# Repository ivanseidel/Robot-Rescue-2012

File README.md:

Robot-Rescue-2012
=================

This repository includes the entire Rescue B project from 2012, used in the international RoboCup Rescue B league.
Our team could acomplish the 3th place in super-team and 1st place of robot design.

There is a currently new version of it (on the picture, the 2013 one), find out more [here](https://github.com/ivanseidel/Robot-Rescue-2013).

This robot was the first Android based robot, that used the cellphone as the main processor and could controll the entirely the robot. We could acomplish heavy calculations using Android's 2.4Ghz processor, creating really "expensive" euristics.

The software has about 12.000 lines of code, written in Java, using Interfaces, and Classes hierarchy to provide well encapsulated code, and easy to use.

The image bellow is the sketch of the sensors/controllers.

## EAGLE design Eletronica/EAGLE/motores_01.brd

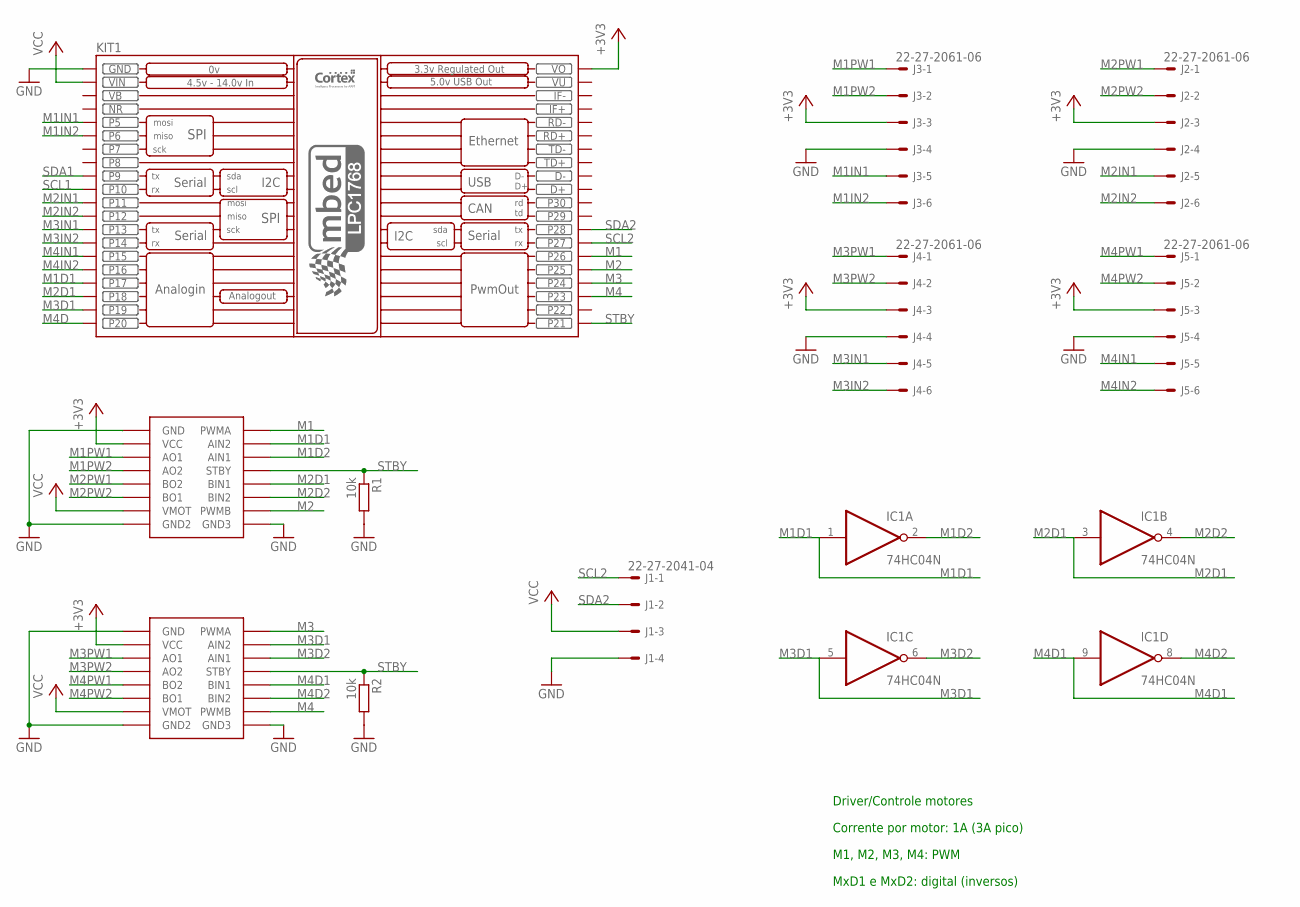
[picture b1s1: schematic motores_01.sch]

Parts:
IC1: 74HC04N; DIL14
J1: 22-27-2041-04; 6410-04
J2, J3, J4, J5: 22-27-2061-06; 6410-06
KIT1: MBED_NXP_LPC1768; MBED-KIT
R1, R2: 10k; 0204/7
U$1, U$2: MOTORDRIVER; 16PH

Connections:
+3V3: J2.3, J3.3, J4.3, J5.3, KIT1.VOUT (VO), U$1.P$2 (VCC), U$2.P$2 (VCC)
GND: IC1.7 (GND), J1.4, J2.4, J3.4, J4.4, J5.4, KIT1.GND, R1.2, R2.2, U$1.P$1 (GND), U$1.P$8 (GND2), U$1.P$9 (GND3), U$2.P$1 (GND), U$2.P$8 (GND2), U$2.P$9 (GND3)
M1: KIT1.P$26 (P26), U$1.P$16 (PWMA)
M1D1: IC1.1 (I), KIT1.P$17 (P17), U$1.P$15 (AIN2)
M1D2: IC1.2 (O), U$1.P$14 (AIN1)
M1IN1: J3.5, KIT1.P$5 (P5)
M1IN2: J3.6, KIT1.P$6 (P6)
M1PW1: J3.1, U$1.P$3 (AO1)
M1PW2: J3.2, U$1.P$4 (AO2)
M2: KIT1.P$25 (P25), U$1.P$10 (PWMB)
M2D1: IC1.3 (I), KIT1.P$18 (P18), U$1.P$12 (BIN1)
M2D2: IC1.4 (O), U$1.P$11 (BIN2)
M2IN1: J2.5, KIT1.P$11 (P11)
M2IN2: J2.6, KIT1.P$12 (P12)
M2PW1: J2.1, U$1.P$5 (BO2)
M2PW2: J2.2, U$1.P$6 (BO1)
M3: KIT1.P$24 (P24), U$2.P$16 (PWMA)
M3D1: IC1.5 (I), KIT1.P$19 (P19), U$2.P$15 (AIN2)
M3D2: IC1.6 (O), U$2.P$14 (AIN1)
M3IN1: J4.5, KIT1.P$13 (P13)
M3IN2: J4.6, KIT1.P$14 (P14)
M3PW1: J4.1, U$2.P$3 (AO1)
M3PW2: J4.2, U$2.P$4 (AO2)
M4: KIT1.P$23 (P23), U$2.P$10 (PWMB)
M4D: KIT1.P$20 (P20)
M4D1: IC1.9 (I), U$2.P$12 (BIN1)
M4D2: IC1.8 (O), U$2.P$11 (BIN2)
M4IN1: J5.5, KIT1.P$15 (P15)
M4IN2: J5.6, KIT1.P$16 (P16)
M4PW1: J5.1, U$2.P$5 (BO2)
M4PW2: J5.2, U$2.P$6 (BO1)
NR: KIT1.NR
SCL1: KIT1.P$10 (P10)
SCL2: J1.1, KIT1.P$27 (P27)
SDA1: KIT1.P$9 (P9)
SDA2: J1.2, KIT1.P$28 (P28)
STBY: KIT1.P$21 (P21), R1.1, R2.1, U$1.P$13 (STBY), U$2.P$13 (STBY)
VB: KIT1.VB
VCC: IC1.14 (VCC), J1.3, KIT1.VIN, U$1.P$7 (VMOT), U$2.P$7 (VMOT)
VU: KIT1.VU

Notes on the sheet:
Driver/Controle motores
Corrente por motor: 1A (3A pico)
M1, M2, M3, M4: PWM
MxD1 e MxD2: digital (inversos)

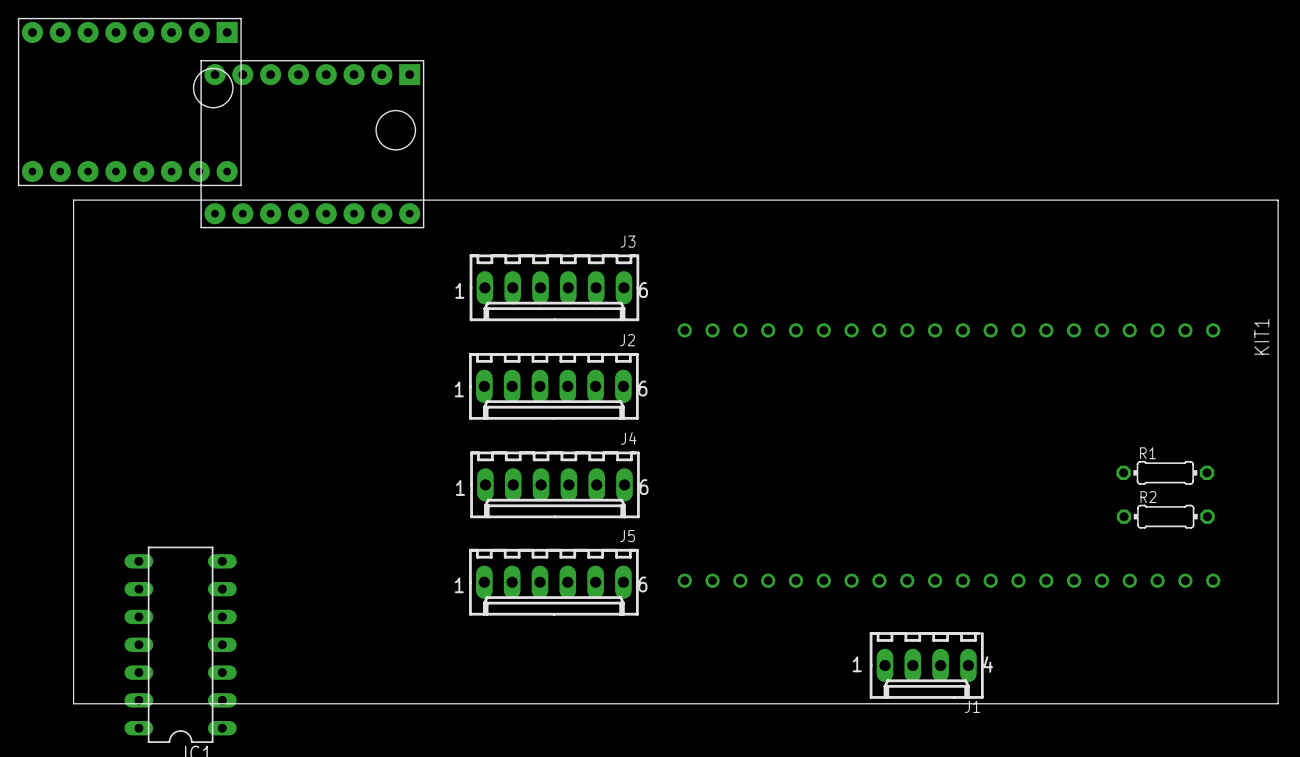
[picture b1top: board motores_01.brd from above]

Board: 2 copper layers, 110.0 x 46.0 mm, 11 parts (0 on the bottom side), 34 nets.

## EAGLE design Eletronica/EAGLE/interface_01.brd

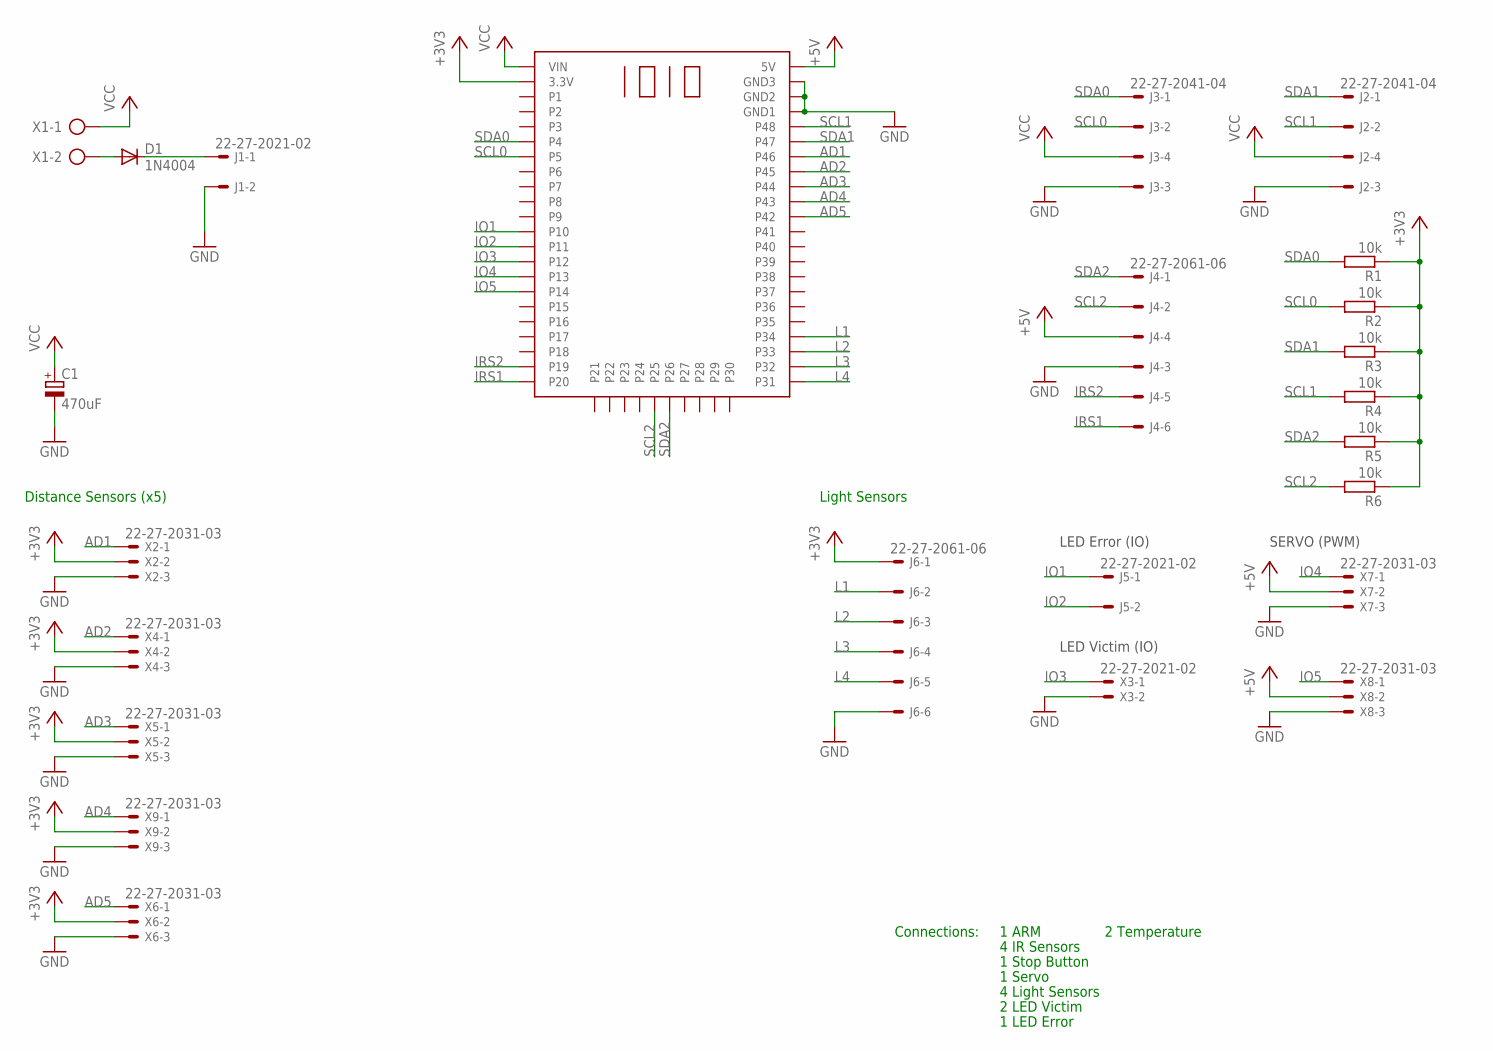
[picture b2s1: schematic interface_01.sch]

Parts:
C1: 470uF; E5-10,5
D1: 1N4004; DO41-10
J1, J5: 22-27-2021-02; 6410-02
J2, J3: 22-27-2041-04; 6410-04
J4, J6: 22-27-2061-06; 6410-06
R1, R2, R3, R4, R5, R6: 10k; 0204/7
U$1: IOIO
X1: AK500/2
X2, X4, X5, X6, X7, X8, X9: 22-27-2031-03; 6410-03
X3: 22-27-2021-02; 6410-02

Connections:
+3V3: J6.1, R1.1, R2.1, R3.1, R4.1, R5.1, R6.1, U$1.P$2 (3.3V), X2.2, X4.2, X5.2, X6.2, X9.2
AD1: U$1.P$48 (P46), X2.1
AD2: U$1.P$47 (P45), X4.1
AD3: U$1.P$46 (P44), X5.1
AD4: U$1.P$45 (P43), X9.1
AD5: U$1.P$44 (P42), X6.1
GND: C1.-, J1.2, J2.3, J3.3, J4.3, J6.6, U$1.P$51 (GND1), U$1.P$52 (GND2), U$1.P$53 (GND3), X2.3, X3.2, X4.3, X5.3, X6.3, X7.3, X8.3, X9.3
IO1: J5.1, U$1.P$12 (P10)
IO2: J5.2, U$1.P$13 (P11)
IO3: U$1.P$14 (P12), X3.1
IO4: U$1.P$15 (P13), X7.1
IO5: U$1.P$16 (P14), X8.1
IRS1: J4.6, U$1.P$22 (P20)
IRS2: J4.5, U$1.P$21 (P19)
L1: J6.2, U$1.P$36 (P34)
L2: J6.3, U$1.P$35 (P33)
L3: J6.4, U$1.P$34 (P32)
L4: J6.5, U$1.P$33 (P31)
unnamed: D1.A, X1.2
unnamed: D1.C, J1.1
unnamed: J4.4, U$1.P$54 (5V), X7.2, X8.2
SCL0: J3.2, R2.2, U$1.P$7 (P5)
SCL1: J2.2, R4.2, U$1.P$50 (P48)
SCL2: J4.2, R6.2, U$1.P$27 (P25)
SDA0: J3.1, R1.2, U$1.P$6 (P4)
SDA1: J2.1, R3.2, U$1.P$49 (P47)
SDA2: J4.1, R5.2, U$1.P$28 (P26)
VCC: C1.+, J2.4, J3.4, U$1.P$1 (VIN), X1.1

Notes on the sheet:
SERVO (PWM)
LED Error (IO)
LED Victim (IO)
Connections:
1 ARM
2 LED Victim
1 LED Error
1 Servo
4 Light Sensors
1 Stop Button
4 IR Sensors
2 Temperature
Distance Sensors (x5)
Light Sensors

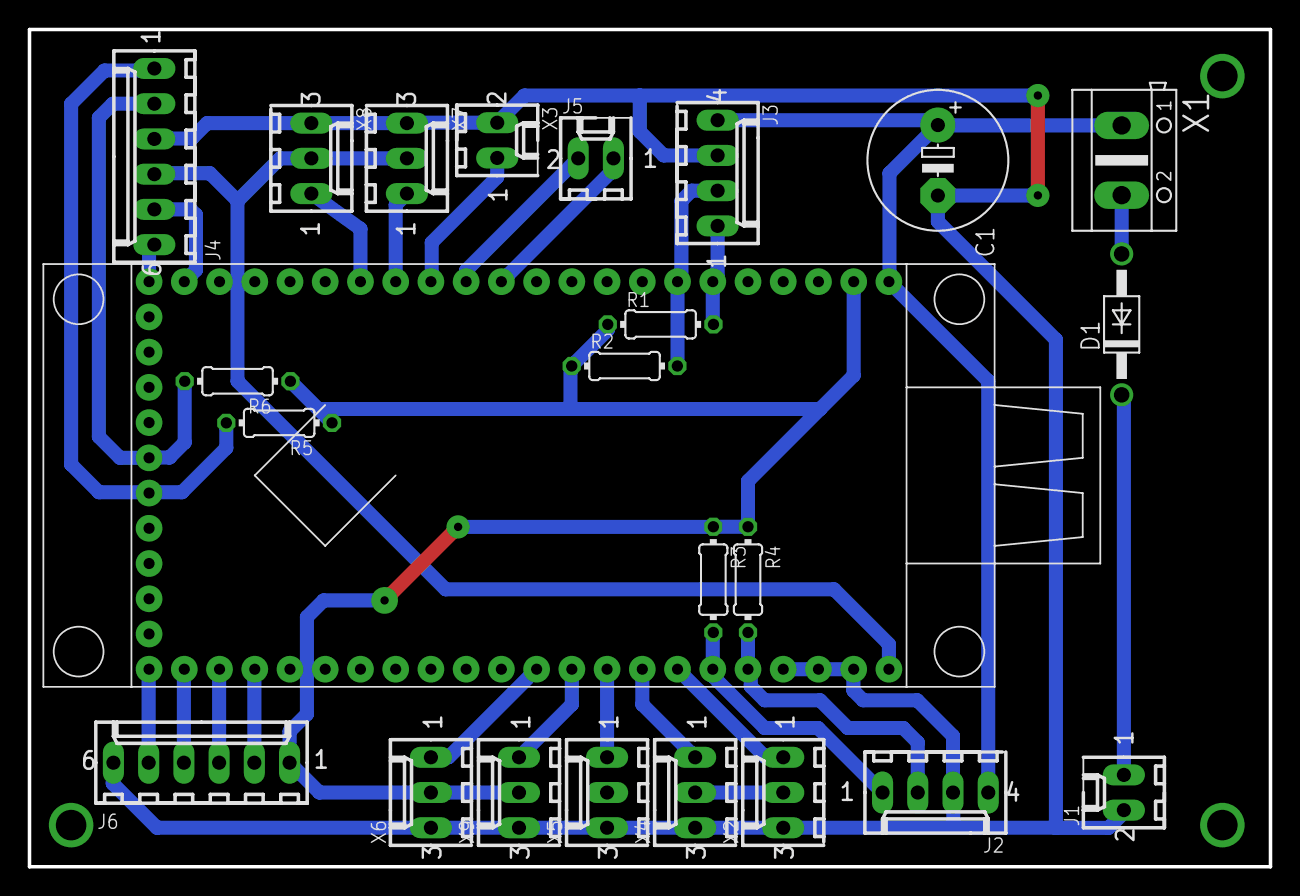
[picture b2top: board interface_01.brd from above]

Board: 2 copper layers, 89.5 x 60.4 mm, 24 parts (0 on the bottom side), 28 nets.

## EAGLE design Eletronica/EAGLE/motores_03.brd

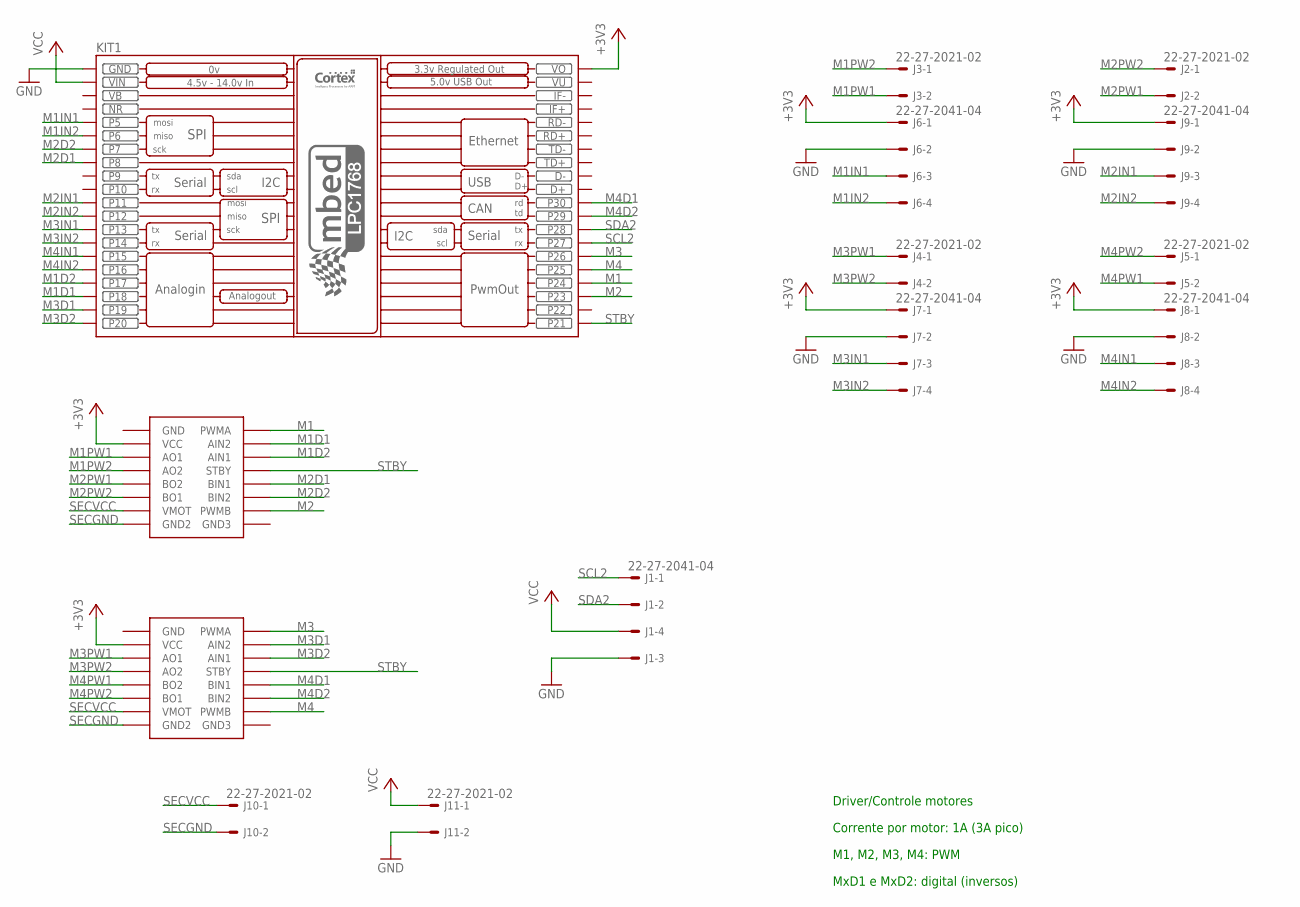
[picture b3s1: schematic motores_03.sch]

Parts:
J1, J6, J7, J8, J9: 22-27-2041-04; 6410-04
J2, J3, J4, J5, J10, J11: 22-27-2021-02; 6410-02
KIT1: MBED_NXP_LPC1768; MBED-KIT
U$1, U$2: MOTORDRIVER; 16PH

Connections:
+3V3: J6.1, J7.1, J8.1, J9.1, KIT1.VOUT (VO), U$1.P$2 (VCC), U$2.P$2 (VCC)
GND: J1.3, J6.2, J7.2, J8.2, J9.2, J11.2, KIT1.GND
M1: KIT1.P$24 (P24), U$1.P$16 (PWMA)
M1D1: KIT1.P$18 (P18), U$1.P$15 (AIN2)
M1D2: KIT1.P$17 (P17), U$1.P$14 (AIN1)
M1IN1: J6.3, KIT1.P$5 (P5)
M1IN2: J6.4, KIT1.P$6 (P6)
M1PW1: J3.2, U$1.P$3 (AO1)
M1PW2: J3.1, U$1.P$4 (AO2)
M2: KIT1.P$23 (P23), U$1.P$10 (PWMB)
M2D1: KIT1.P$8 (P8), U$1.P$12 (BIN1)
M2D2: KIT1.P$7 (P7), U$1.P$11 (BIN2)
M2IN1: J9.3, KIT1.P$11 (P11)
M2IN2: J9.4, KIT1.P$12 (P12)
M2PW1: J2.2, U$1.P$5 (BO2)
M2PW2: J2.1, U$1.P$6 (BO1)
M3: KIT1.P$26 (P26), U$2.P$16 (PWMA)
M3D1: KIT1.P$19 (P19), U$2.P$15 (AIN2)
M3D2: KIT1.P$20 (P20), U$2.P$14 (AIN1)
M3IN1: J7.3, KIT1.P$13 (P13)
M3IN2: J7.4, KIT1.P$14 (P14)
M3PW1: J4.1, U$2.P$3 (AO1)
M3PW2: J4.2, U$2.P$4 (AO2)
M4: KIT1.P$25 (P25), U$2.P$10 (PWMB)
M4D1: KIT1.P$30 (P30), U$2.P$12 (BIN1)
M4D2: KIT1.P$29 (P29), U$2.P$11 (BIN2)
M4IN1: J8.3, KIT1.P$15 (P15)
M4IN2: J8.4, KIT1.P$16 (P16)
M4PW1: J5.2, U$2.P$5 (BO2)
M4PW2: J5.1, U$2.P$6 (BO1)
NR: KIT1.NR
SCL2: J1.1, KIT1.P$27 (P27)
SDA2: J1.2, KIT1.P$28 (P28)
SECGND: J10.2, U$1.P$8 (GND2), U$2.P$8 (GND2)
SECVCC: J10.1, U$1.P$7 (VMOT), U$2.P$7 (VMOT)
STBY: KIT1.P$21 (P21), U$1.P$13 (STBY), U$2.P$13 (STBY)
VB: KIT1.VB
VCC: J1.4, J11.1, KIT1.VIN
VU: KIT1.VU

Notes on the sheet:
Driver/Controle motores
Corrente por motor: 1A (3A pico)
M1, M2, M3, M4: PWM
MxD1 e MxD2: digital (inversos)

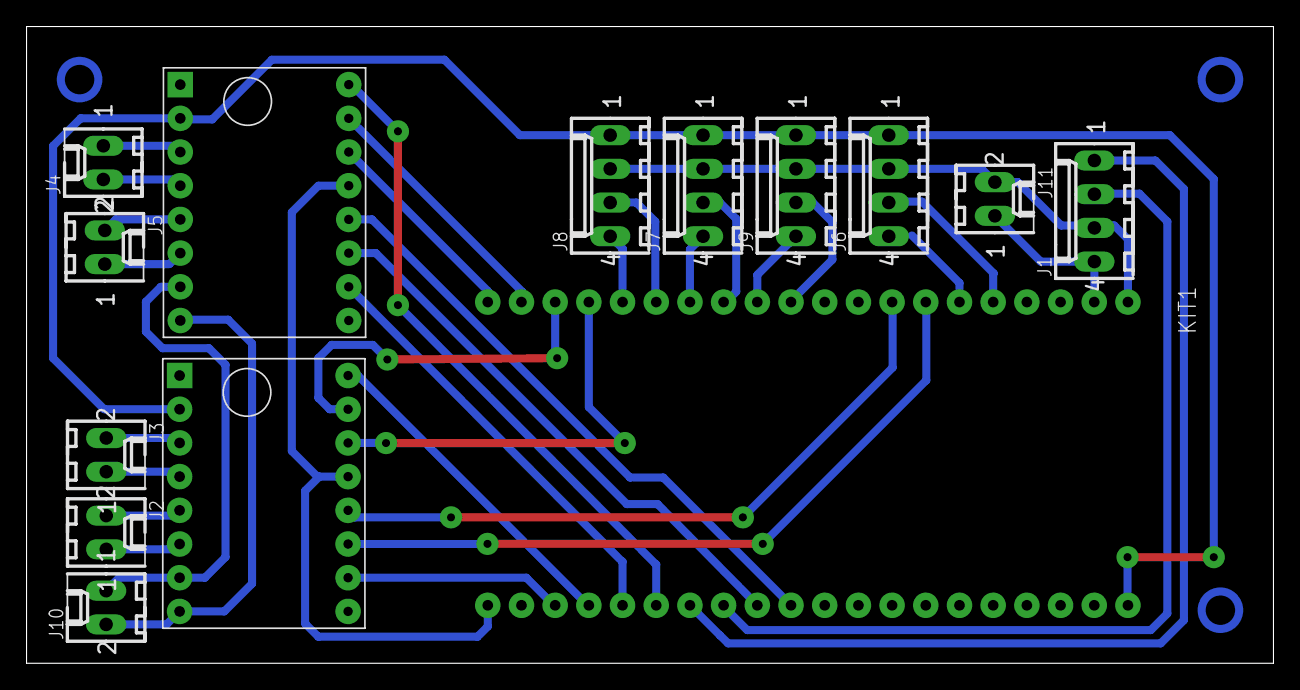
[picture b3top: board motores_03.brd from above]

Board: 2 copper layers, 94.0 x 48.0 mm, 14 parts (0 on the bottom side), 36 nets.

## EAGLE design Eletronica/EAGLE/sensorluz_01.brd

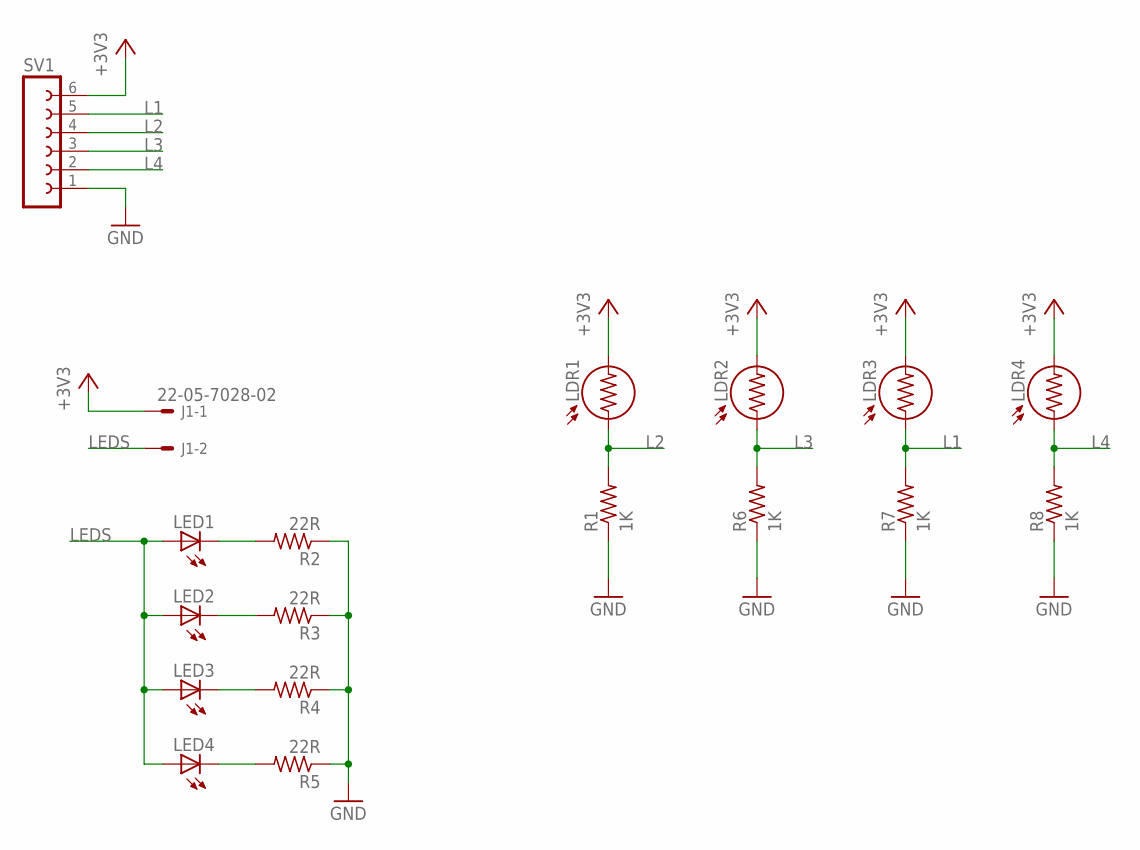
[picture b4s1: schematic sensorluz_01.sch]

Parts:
J1: 22-05-7028-02; 7395-02
LDR1, LDR2, LDR3, LDR4: LDR5MM; LDR338-54C
LED1, LED2, LED3, LED4: LED5MM
R1, R6, R7, R8: 1K; 0204/5
R2, R3, R4, R5: 22R; 0204/5
SV1: FE06W

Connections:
+3V3: J1.1, LDR1.2, LDR2.2, LDR3.2, LDR4.2, SV1.6
GND: R1.1, R2.1, R3.1, R4.1, R5.1, R6.1, R7.1, R8.1, SV1.1
L1: LDR3.1, R7.2, SV1.5
L2: LDR1.1, R1.2, SV1.4
L3: LDR2.1, R6.2, SV1.3
L4: LDR4.1, R8.2, SV1.2
LEDS: J1.2, LED1.A, LED2.A, LED3.A, LED4.A
unnamed: LED1.K (C), R2.2
unnamed: LED2.K (C), R3.2
unnamed: LED3.K (C), R4.2
unnamed: LED4.K (C), R5.2

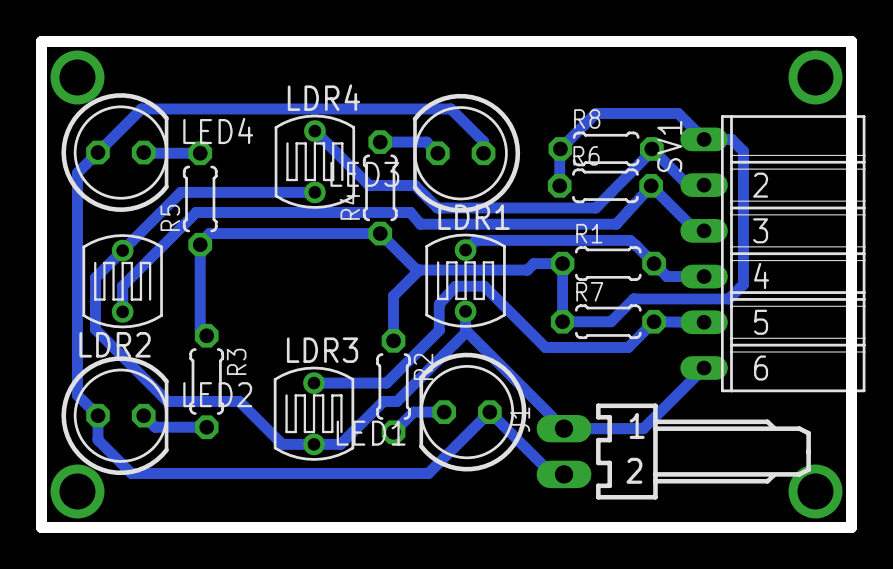
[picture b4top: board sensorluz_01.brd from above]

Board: 2 copper layers, 45.0 x 27.0 mm, 18 parts (0 on the bottom side), 11 nets.

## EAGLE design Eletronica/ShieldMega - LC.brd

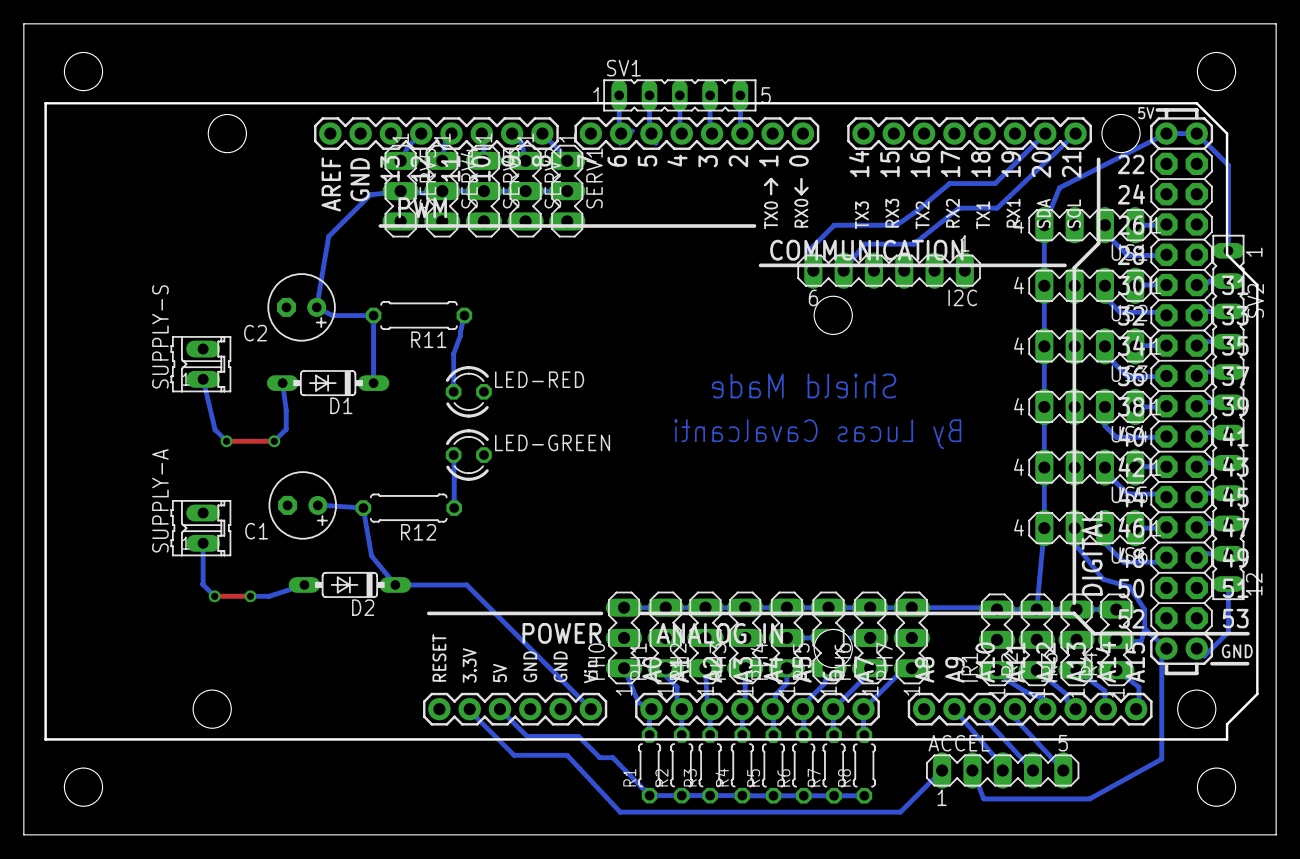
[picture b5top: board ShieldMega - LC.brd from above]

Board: 2 copper layers, 105.0 x 68.0 mm, 46 parts (0 on the bottom side), 59 nets.

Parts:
ACCEL: MA05-1
C1, C2: E2,5-6
D1, D2: 1N4148DO35-7; DO35-7
I2C: MA06-1
IR1, IR2, IR3, IR4: MA03-1
LED-GREEN: LED3MM
LED-RED: LED3MM
PH0, PH1, PH2, PH3, PH4, PH5, PH6, PH7: MA03-1
R1, R2, R3, R4, R5, R6, R7, R8: 0204/5
R11, R12: 200; 0207/7
SERV1, SERV2, SERV3, SERV4, SERV5: MA03-1
SUPPLY-A: 02P
SUPPLY-S: 02P
SV1: FE05-1
SV2: FE12
U1: ARDUINO-MEGAFULL; ARDUINO_MEGA
US1, US2, US3, US4, US5, US6: MA04-1

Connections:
3V3: ACCEL.1, U1.3.3V
5V: R1.1, R2.1, R3.1, R4.1, R5.1, R6.1, R7.1, R8.1, U1.5V@0
5VU: IR1.3, IR2.3, IR3.3, IR4.3, PH0.3, PH1.3, PH2.3, PH3.3, PH4.3, PH5.3, PH6.3, PH7.3, SV2.1, U1.5V@1, U1.5V@2, US1.4, US2.4, US3.4, US4.4, US5.4, US6.4
31: SV2.2, U1.31
33: SV2.3, U1.33
35: SV2.4, U1.35
37: SV2.5, U1.37
39: SV2.6, U1.39
41: SV2.7, U1.41
43: SV2.8, U1.43
45: SV2.9, U1.45
47: SV2.10, U1.47
49: SV2.11, U1.49
A0: PH0.1, R1.2, U1.A0
A1: PH1.1, R2.2, U1.A1
A2: PH2.1, R3.2, U1.A2
A3: PH3.1, R4.2, U1.A3
A4: PH4.1, R5.2, U1.A4
A5: PH5.1, R6.2, U1.A5
A6: PH6.1, R7.2, U1.A6
A7: PH7.1, R8.2, U1.A7
ECHO1: U1.28, US1.2
ECHO2: U1.32, US2.2
ECHO3: U1.36, US3.2
ECHO4: U1.40, US4.2
ECHO5: U1.44, US5.2
ECHO6: U1.48, US6.2
GND: ACCEL.2, C1.-, C2.-, I2C.2, I2C.3, IR1.2, IR2.2, IR3.2, IR4.2, LED-GREEN.K, LED-RED.K, PH0.2, PH1.2, PH2.2, PH3.2, PH4.2, PH5.2, PH6.2, PH7.2, SERV1.3, SERV2.3, SERV3.3, SERV4.3, SERV5.3, SUPPLY-A.2, SUPPLY-S.2, SV2.12, U1.GND@0, U1.GND@1, U1.GND@2, U1.GND@3, U1.GND@4, US1.3, US2.3, US3.3, US4.3, US5.3, US6.3
IR1: IR1.1, U1.A12
IR2: IR2.1, U1.A13
IR3: IR3.1, U1.A14
IR4: IR4.1, U1.A15
unnamed: D2.A, SUPPLY-A.1
unnamed: SV1.5, U1.2
unnamed: D1.A, SUPPLY-S.1
unnamed: SV1.4, U1.3
unnamed: SV1.3, U1.4
unnamed: SV1.2, U1.5
unnamed: SV1.1, U1.6
unnamed: LED-GREEN.A, R12.1
unnamed: LED-RED.A, R11.1
PWM1: SERV1.1, U1.8
PWM2: SERV2.1, U1.9
PWM3: SERV3.1, U1.10
PWM4: SERV4.1, U1.11
PWM5: SERV5.1, U1.12
SCL: I2C.5, U1.21
SDA: I2C.6, U1.20
TRIG1: U1.26, US1.1
TRIG2: U1.30, US2.1
TRIG3: U1.34, US3.1
TRIG4: U1.38, US4.1
TRIG5: U1.42, US5.1
TRIG6: U1.46, US6.1
VIN-A: C1.+, D2.C, R12.2, U1.VIN
VIN-S: C2.+, D1.C, R11.2, SERV1.2, SERV2.2, SERV3.2, SERV4.2, SERV5.2
X: ACCEL.3, U1.A9
Y: ACCEL.4, U1.A10
Z: ACCEL.5, U1.A11

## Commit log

2013-12-17 General files upload
2013-12-17 Electronics upload
2013-12-17 Mechanics upload
2013-12-17 Research and test files
2013-12-17 Midia files upload
    Infographics, renders, pictures and logos
2013-12-17 Clean files
2013-12-17 Software upload

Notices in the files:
parts and their libraries:
SparkFun-Boards: Licensing: CC v3.0 Share-Alike You are welcome to use this library for commercial purposes.
